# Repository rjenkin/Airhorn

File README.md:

Airhorn
=======

Code to activate a 12 volt Airhorn using Raspberry Pi

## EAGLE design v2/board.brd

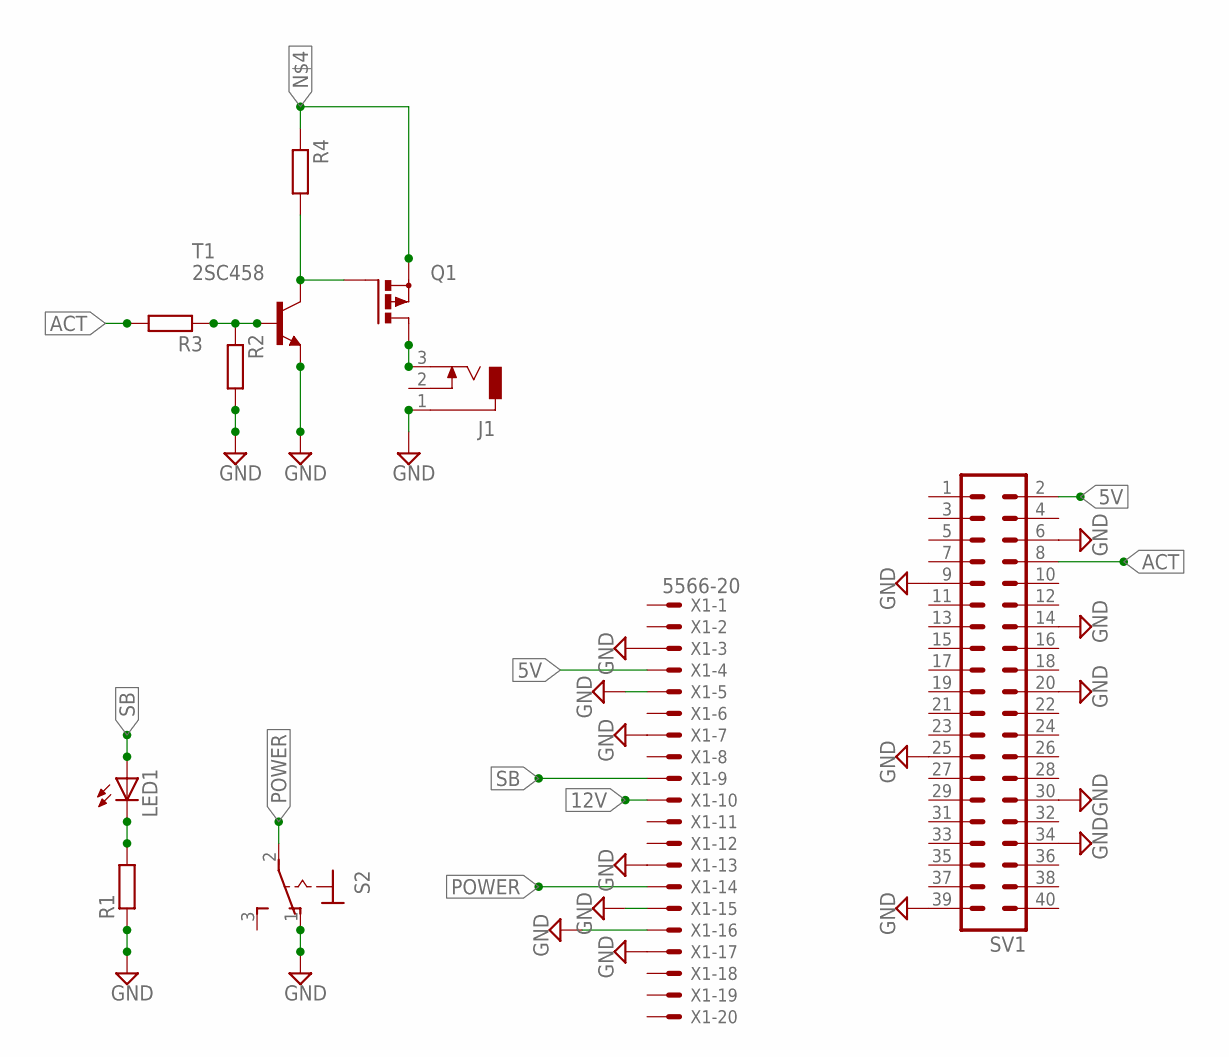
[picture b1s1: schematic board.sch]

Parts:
J1: DCJ0303
LED1: LED_ELD260; LED_LD260
Q1: PMOSFET_PTO220BV; TO220BV
R1, R2, R3, R4: R-EU_0309/10; 0309/10
S2: 320-916
SV1: MA20-2
T1: 2SC458; TO92-ECB
X1: 5566-20

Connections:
5V: SV1.2, X1.4
12V: X1.10
ACT: R3.2, SV1.8
GND: J1.1, R1.1, R2.2, S2.1 (O), SV1.6, SV1.9, SV1.14, SV1.20, SV1.25, SV1.30, SV1.34, SV1.39, T1.E, X1.3, X1.5, X1.7, X1.13, X1.15, X1.16, X1.17
unnamed: LED1.K (C), R1.2
unnamed: R2.1, R3.1, T1.B
unnamed: Q1.G, R4.2, T1.C
unnamed: Q1.S, R4.1
unnamed: J1.3, Q1.D
POWER: S2.2, X1.14
SB: LED1.A, X1.9

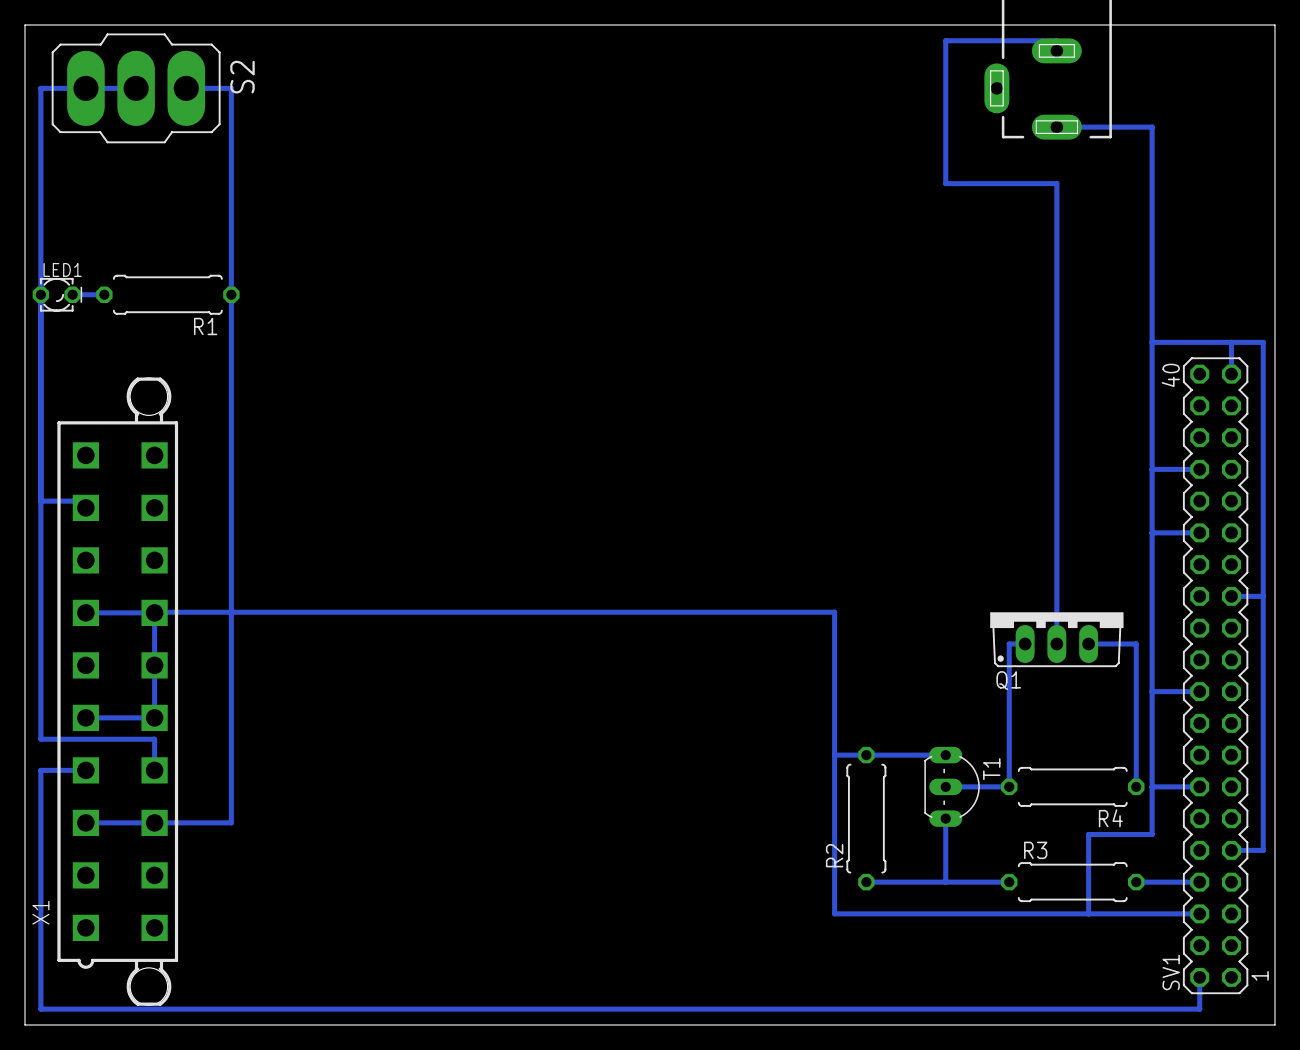
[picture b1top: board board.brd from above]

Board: 2 copper layers, 100.0 x 80.0 mm, 11 parts (0 on the bottom side), 10 nets.

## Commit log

2013-07-12 Creates socket, listens for activation requests, activates airhorn
2013-07-12 A PHP webpage that can send an Airhorn activation requests
2022-01-28 Added docs and v2 schematic
